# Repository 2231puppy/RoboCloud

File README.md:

# RoboCloud

## What is this?

2231puppy's Project Stida RoboCloud is an ESP32-S2 robot controller board. It has Wi-Fi courtesy of the ESP32-S2 and can drive 2 4.5A (max) motors. It has a bunch of exposed IO and can handle up to 20V in. It is designed for use with Adafruit's CircuitPython.

## What's Project Stida?

Stida was 2231puppy's first robot. While no longer in use, the name lives on in Project Stida, 2231puppy's organization.

## Why would I want it?

Well, that's simple. It's a relatively low-cost board that can be used to easily build robots that are IoT-connected. Did I mention it's super easy to program because of the awesome work at [Adafruit](https://adafruit.com) on CircuitPython?

## Great! So, where can I get one?

This is the sad part :( There is currently nowhere to purcase this board, but the source KiCad v5.1.9 files are right here in this repo. Feel free to make them yourself! I'm working on an accurate BOM.

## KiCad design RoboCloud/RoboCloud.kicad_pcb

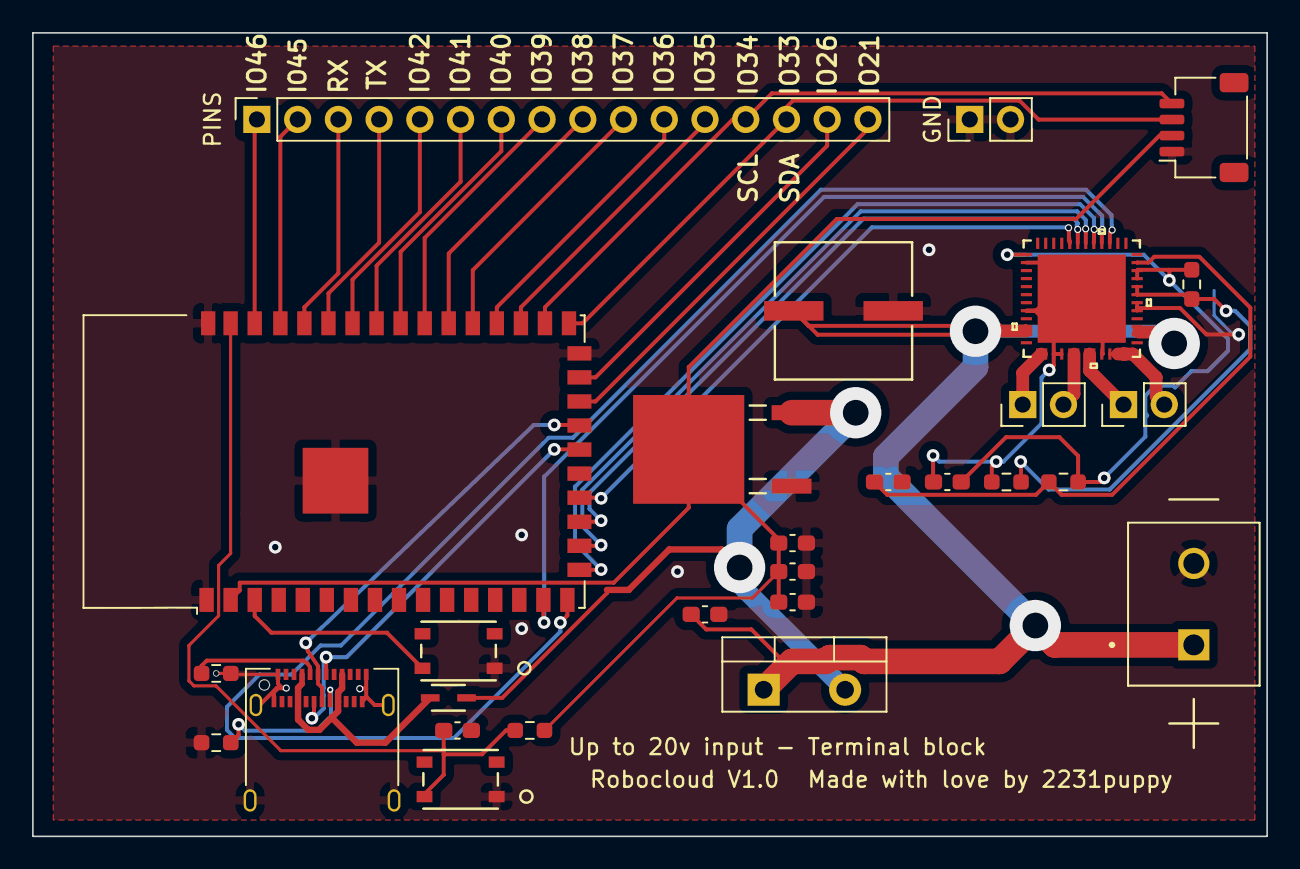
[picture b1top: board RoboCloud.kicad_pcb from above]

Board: 2 copper layers, 77.0 x 50.1 mm, 26 parts (0 on the bottom side), 41 nets.

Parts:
C: C_0603_1608Metric_Pad1.08x0.95mm_HandSolder
C1: 270pF; C_0603_1608Metric_Pad1.08x0.95mm_HandSolder
C2: 100µF; UUD1H101MNL1GS
C3, C4, C5: 0.1µF; C_0603_1608Metric_Pad1.08x0.95mm_HandSolder
C6: 10µF; C_0603_1608Metric_Pad1.08x0.95mm_HandSolder
C7: 10μF; C_0603_1608Metric_Pad1.08x0.95mm_HandSolder
D1: DIODE; TO-220-2_Vertical
D2: DIODE; 1N4148WX-TP
GND: Conn_01x02_Female; PinHeader_1x02_P2.54mm_Vertical
J2: Barrel_Jack; CUI_TB006-508-02BE
J3: USB_C_Receptacle; USB_C_Receptacle_Amphenol_12401610E4-2A
M1, M2: Motor_DC; PinHeader_1x02_P2.54mm_Vertical
PINS: Conn_01x16_Female; PinSocket_1x16_P2.54mm_Vertical
R1: 10kΩ; R_0603_1608Metric_Pad0.98x0.95mm_HandSolder
R2, R4, R5: 5.1kΩ; R_0603_1608Metric_Pad0.98x0.95mm_HandSolder
Re: 10kΩ; R_0603_1608Metric_Pad0.98x0.95mm_HandSolder
SW1, SW1#2: SW_Push; PTS815 SJM 250 SMTR LFS
U1: TB67H420FTG_EL
U1#2: NCP1117DT33T5G
U2: ESP32-S2-WROVER

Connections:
GND: C.2, C1.2, C2.2, C3.1, C5.2, C6.2, C7.2, GND.1, GND.2, J2.2, J3.A1, J3.A12, J3.B1, J3.B12, J3.S1, R4.1, R5.1, SW1.1, SW1#2.1, U1.29, U1.30, U1#2.1, U2.1, U2.26, U2.42, U2.43
unnamed: C1.1, R2.2, U1.35
unnamed: C2.1, C3.2, D1.1, J2.1, U1.10, U1.11, U1.26, U1.27
unnamed: C4.1, R1.1, U1.2, U1.8, U1.15, U1.16, U1.21, U1.49
unnamed: C4.2, R2.1, Re.1, U1.1, U1.33, U1.34
unnamed: C5.1, C6.1, C7.1, U1#2.2, U2.2
unnamed: D1.2, D2.2, U1#2.3
unnamed: D2.1, J3.A4, J3.A9, J3.B4, J3.B9
unnamed: PINS.1, U2.40
unnamed: PINS.2, U2.39
unnamed: PINS.3, U2.38
unnamed: PINS.4, U2.37
unnamed: PINS.5, U2.36
unnamed: PINS.6, U2.35
unnamed: PINS.7, U2.34
unnamed: PINS.8, U2.33
unnamed: PINS.9, U2.32
unnamed: PINS.10, U2.31
unnamed: PINS.11, U2.30
unnamed: PINS.12, U2.29
unnamed: PINS.13, U2.28
unnamed: PINS.14, U2.27
unnamed: PINS.15, U2.25
unnamed: PINS.16, U2.24
unnamed: J3.A5, R4.2
unnamed: J3.A6, J3.B6, U2.23
unnamed: J3.A7, J3.B7, U2.22
unnamed: J3.B5, R5.2
unnamed: M1.1, U1.13, U1.14
unnamed: M1.2, U1.17, U1.18
unnamed: M2.1, U1.19, U1.20
unnamed: M2.2, U1.22, U1.23, U1.24
unnamed: R1.2, Re.2, U1.31, U1.32
unnamed: SW1#2.2, U2.3
unnamed: U1.39, U2.16
unnamed: U1.40, U2.15
unnamed: U1.41, U2.17
unnamed: U1.42, U2.18
unnamed: U1.43, U2.19
unnamed: U1.44, U2.20
SW2-Pad2: C.1, SW1.2, U2.41

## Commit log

2022-01-21 [ImgBot] Optimize images
    *Total -- 738.43kb -> 624.03kb (15.49%)
    /RoboCloud/out/svg/RoboCloud-B_Adhes.svg -- 1.07kb -> 0.32kb (70.14%)
    /RoboCloud/out/svg/RoboCloud-B_Paste.svg -- 1.07kb -> 0.32kb (70.14%)
    /RoboCloud/out/svg/RoboCloud-F_Adhes.svg -- 1.07kb -> 0.32kb (70.14%)
    /RoboCloud/out/svg/RoboCloud-B_Fab.svg -- 1.05kb -> 0.32kb (69.71%)
    /RoboCloud/out/svg/RoboCloud-Edge_Cuts.svg -- 1.36kb -> 0.60kb (56.08%)

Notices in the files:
parts and their libraries:
Copyright 2016 Accelerated Designs. All rights reserved.
